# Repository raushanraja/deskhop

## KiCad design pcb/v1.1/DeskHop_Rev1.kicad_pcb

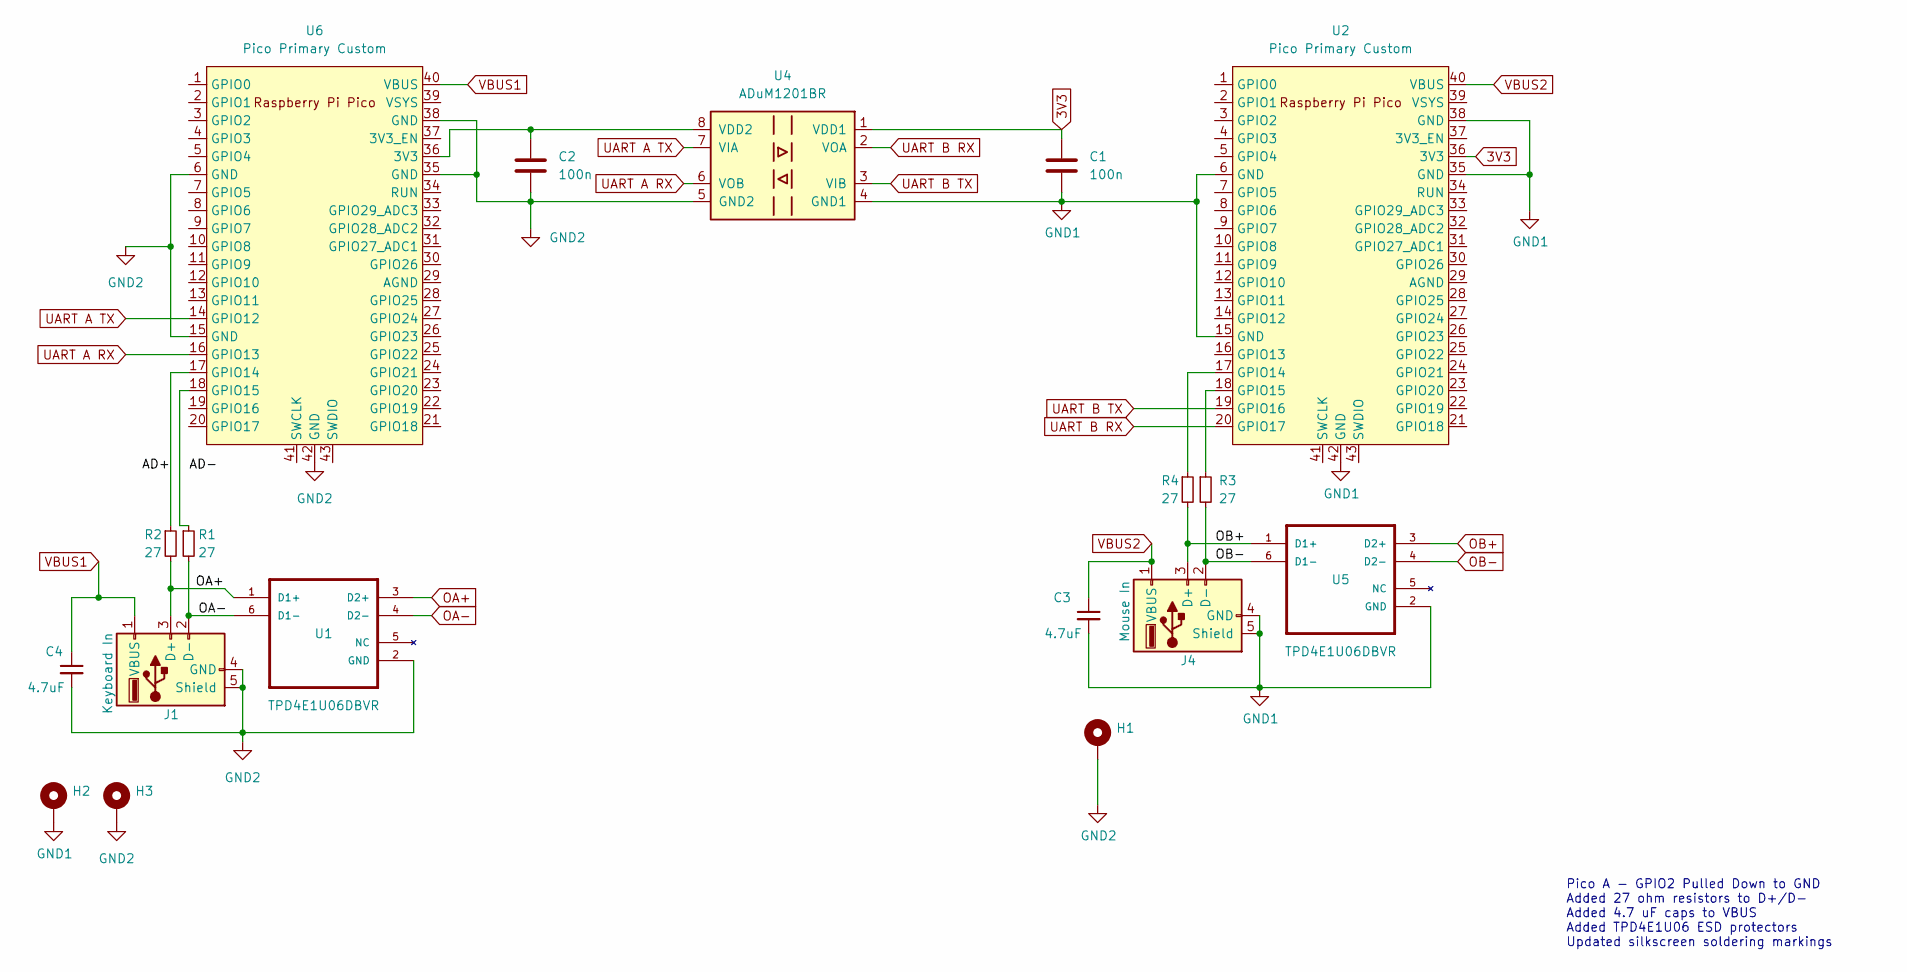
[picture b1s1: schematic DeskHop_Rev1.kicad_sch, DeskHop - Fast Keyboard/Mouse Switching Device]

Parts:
C1, C2: 100n; C_1206_3216Metric_Pad1.33x1.80mm_HandSolder
C3, C4: 4.7uF; C_1206_3216Metric_Pad1.33x1.80mm_HandSolder
H1, H2, H3: MountingHole_Pad; MountingHole_2.7mm_M2.5_Pad_TopBottom
J1: Keyboard In; USB_A_Molex_67643_Horizontal
J4: Mouse In; USB_A_Molex_67643_Horizontal
R1, R2, R3, R4: 27; R_1206_3216Metric_Pad1.30x1.75mm_HandSolder
U1, U5: TPD4E1U06DBVR; DBV6_TEX
U2, U6: Pico Primary Custom; RPi_Pico_USBC_CUSTOM_SMD_TH
U4: ADuM1201BR; SOIC-8_3.9x4.9mm_P1.27mm

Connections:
3V3: C1.1, U2.36 (3V3), U4.1 (VDD1)
/AD+: R2.1, U6.17 (GPIO14)
GND1: C1.2, C3.2, H2.1, J4.4 (GND), J4.5 (Shield), U2.6 (GND), U2.15 (GND), U2.35 (GND), U2.38 (GND), U2.42 (GND), U4.4 (GND1), U5.2 (GND)
GND2: C2.2, C4.2, H1.1, H3.1, J1.4 (GND), J1.5 (Shield), U1.2 (GND), U4.5 (GND2), U6.6 (GND), U6.15 (GND), U6.35 (GND), U6.38 (GND), U6.42 (GND)
unnamed: R4.1, U2.17 (GPIO14)
unnamed: R3.1, U2.18 (GPIO15)
unnamed: C2.1, U4.8 (VDD2), U6.36 (3V3)
unnamed: R1.1, U6.18 (GPIO15)
OA+: J1.3 (D+), R2.2, U1.1 (D1+), U1.3 (D2+)
OA-: J1.2 (D-), R1.2, U1.4 (D2-), U1.6 (D1-)
OB+: J4.3 (D+), R4.2, U5.1 (D1+), U5.3 (D2+)
OB-: J4.2 (D-), R3.2, U5.4 (D2-), U5.6 (D1-)
UART A RX: U4.6 (VOB), U6.16 (GPIO13)
UART A TX: U4.7 (VIA), U6.14 (GPIO12)
UART B RX: U2.20 (GPIO17), U4.2 (VOA)
UART B TX: U2.19 (GPIO16), U4.3 (VIB)
VBUS1: C4.1, J1.1 (VBUS), U6.40 (VBUS)
VBUS2: C3.1, J4.1 (VBUS), U2.40 (VBUS)

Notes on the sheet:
Pico A - GPIO2 Pulled Down to GND Added 27 ohm resistors to D+/D- Added 4.7 uF caps to VBUS Added TPD4E1U06 ESD protectors Updated silkscreen soldering markings

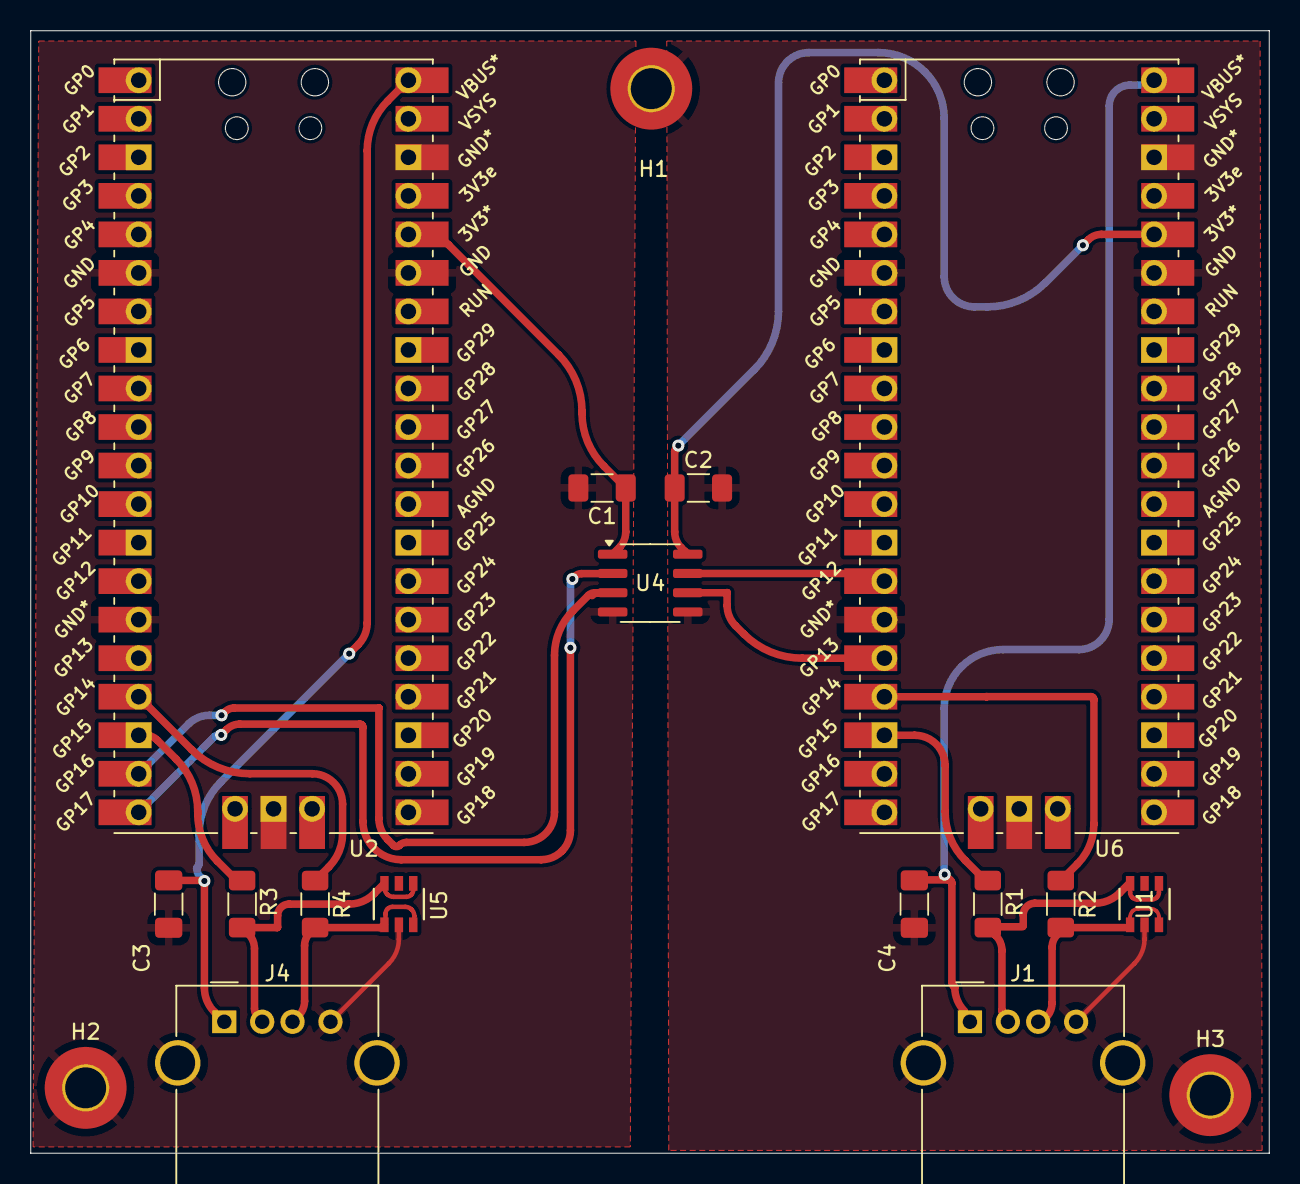
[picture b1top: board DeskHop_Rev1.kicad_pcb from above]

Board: 2 copper layers, 81.7 x 74.0 mm, 18 parts (0 on the bottom side), 18 nets.

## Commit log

2024-09-10 update smd r/c to 1206 size
2024-09-11 initial rework, connection to be reviewed
2024-09-11 somewhat verOneZeroOne
2024-09-11 ver OneXeroOne
2024-10-19 match pins to original board
